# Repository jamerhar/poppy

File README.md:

# Poppy
### 70% Alice keyboard using THT components expanding upon [elmo's Sesame](https://github.com/kb-elmo/sesame).

### Expanding upon the Sesame, the Poppy includes a function row, solenoid support, and a resin printable case.

### Board Bill of Materials
 |Count|Part|Reference|
 |-|-|-|
 |1|ATmega32A 40 Pin DIP|U1|
 |1|40 Pin DIP Socket|U1|
 |1|USB4085-GF-A USB Type-C|J1|
 |1|500mA Polyfuse|F1|
 |2|6mm Push Button|SW1, SW2|
 |1|16MHz Quartz Crystal|X1|
 |1|4.7uF Electrolytic Capacitor|C1|
 |2|0.1uF Ceramic Disk Capacitor|C2,C3|
 |2|22pF Ceramic Disk Capacitor|C4,C5|
 |1|1.5kΩ Resistor|R1|
 |2|68Ω Resistor|R2,R3|
 |2|5.1kΩ Resistor|R4,R5|
 |1|10kΩ Resistor|R6|
 |2|3.6V Zener Diode (DO-35 BZX55C3V6)|D77,D78|
 |76|Universal Switching Diode (DO-35 1N4148)|D1-D76|
 
 This bill of materials is identical to the Sesame's minus the quantity of diodes.
 
 ### Solenoid Bill of Materials
 |Count|Part|Reference|
 |-|-|-|
 |1|Uxcell Mini Push 4.5V @ ~350mA Solenoid| |
 |1|1N4001 Diode|D1|
 |1|TIP120 Transistor|Q1|
 |1|2.2kΩ Resistor|R1|
 
 The solenoid, [purchasable on Amazon](https://www.amazon.com/gp/product/B013DR655A/ref=ppx_yo_dt_b_search_asin_title?ie=UTF8&psc=1), addon is optional and does not employ the most polished mounting and connection to the main PCB, but is functional and supported in both QMK/VIAL firmware. The easiest method is to run wires from the ATmega32A's solenoid pin (B4/pin 5) and +5V and GND from the ISP header above the 32A. Some slight changes to the PCB could be made to add a header or JST connector to the solenoid, but I haven't gotten around to it at this time.
 
 ### Case Bill of Materials
  |Count|Part|
  |-|-|
  |1|PCB|
  |1|Plate|
  |1|Bottom Case (3D/Resin Printed)|
  |1|Top Case (3D/Resin Printed)|
  |1|Weight|
  |4|10mm Diameter Adhesive Bumpons|
  |19|Brass Screw-to-Expand Inserts, M2x4mm|
  |19|M2x5mm Button Head Screw|
  |1|Solenoid Daugherboard PCB (Optional)|
  |1|Solenoid Driver PCB (Optional)|
  |2|M2x3mm Socket/Button Head Screw (Optional)|
  
  8 M2x5mm screws and screw-to-expend inserts, [purchasable on McMaster](https://www.mcmaster.com/94510A611/), are used to secure both halves of the case. 4 M2x5mm screws and inserts are used to secure the plate to the top case. 5 M2x5mm screws and inserts are used to secure the optional solenoid/driver board to the bottom case. 2 M2x3mm screws are used to secure the solenoid to the solenoid daughterboard. 2 M2x5mm screws are used to secure the weight to the bottom case, countersunk holes can be drilled and flat head screws can be used for a flush look. I had my case printed through JLCPCB's resin 3D printing services since I don't have a printer large enough for this board. I've had successful prints with both 8000 resin and 8111X resin, with the latter being cheaper. There is a small amount of warping throughout the thin F-row separating area on both of my prints due to the extremely thin geometry, but it does not interfere during use (YMMV). 
  
### Disclaimer
I do not offer any sort of warranty, nor can I be held liable if something goes wrong.
Please thoroughly review the design, especially involving the case, before ordering anything. There are possibly small errors and other defects within the design, this was my first attempt at case design and it is by no means perfect.

### Additional Images
One revision out of date bottom case:

Weight and solenoid driver wiring:

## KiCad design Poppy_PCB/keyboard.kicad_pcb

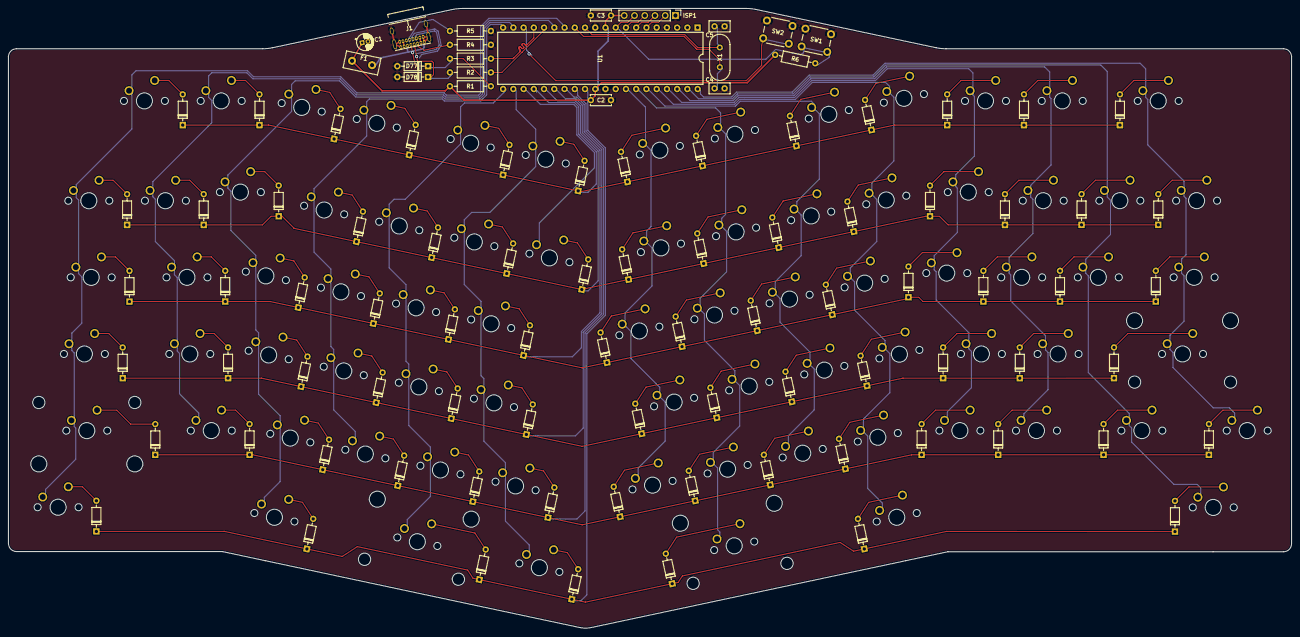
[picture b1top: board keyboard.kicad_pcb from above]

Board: 2 copper layers, 318.4 x 153.8 mm, 172 parts (0 on the bottom side), 113 nets.

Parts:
C1: 4.7u; CP_Radial_D4.0mm_P1.50mm
C2, C3: 0.1u; C_Disc_D5.0mm_W2.5mm_P5.00mm
C4, C5: 22p; C_Disc_D5.0mm_W2.5mm_P2.50mm
D1: F1; D_DO-35_SOD27_P7.62mm_Horizontal
D2: F2; D_DO-35_SOD27_P7.62mm_Horizontal
D3: F3; D_DO-35_SOD27_P7.62mm_Horizontal
D4: F4; D_DO-35_SOD27_P7.62mm_Horizontal
D5: F5; D_DO-35_SOD27_P7.62mm_Horizontal
D6: F6; D_DO-35_SOD27_P7.62mm_Horizontal
D7: F7; D_DO-35_SOD27_P7.62mm_Horizontal
D8: F8; D_DO-35_SOD27_P7.62mm_Horizontal
D9: F9; D_DO-35_SOD27_P7.62mm_Horizontal
D10: F10; D_DO-35_SOD27_P7.62mm_Horizontal
D11: F11; D_DO-35_SOD27_P7.62mm_Horizontal
D12: F12; D_DO-35_SOD27_P7.62mm_Horizontal
D13: F13; D_DO-35_SOD27_P7.62mm_Horizontal
D14: ESC; D_DO-35_SOD27_P7.62mm_Horizontal
D15: 1; D_DO-35_SOD27_P7.62mm_Horizontal
D16: 2; D_DO-35_SOD27_P7.62mm_Horizontal
D17: 3; D_DO-35_SOD27_P7.62mm_Horizontal
D18: 4; D_DO-35_SOD27_P7.62mm_Horizontal
D19: 5; D_DO-35_SOD27_P7.62mm_Horizontal
D20: 6; D_DO-35_SOD27_P7.62mm_Horizontal
D21: 7; D_DO-35_SOD27_P7.62mm_Horizontal
D22: 8; D_DO-35_SOD27_P7.62mm_Horizontal
D23: 9; D_DO-35_SOD27_P7.62mm_Horizontal
D24: 0; D_DO-35_SOD27_P7.62mm_Horizontal
D25: MINS; D_DO-35_SOD27_P7.62mm_Horizontal
D26: EQL; D_DO-35_SOD27_P7.62mm_Horizontal
D27: BSLS; D_DO-35_SOD27_P7.62mm_Horizontal
D28: DEL; D_DO-35_SOD27_P7.62mm_Horizontal
D29: TAB; D_DO-35_SOD27_P7.62mm_Horizontal
D30: Q; D_DO-35_SOD27_P7.62mm_Horizontal
D31: W; D_DO-35_SOD27_P7.62mm_Horizontal
D32: E; D_DO-35_SOD27_P7.62mm_Horizontal
D33: R; D_DO-35_SOD27_P7.62mm_Horizontal
D34: T; D_DO-35_SOD27_P7.62mm_Horizontal
D35: Y; D_DO-35_SOD27_P7.62mm_Horizontal
D36: U; D_DO-35_SOD27_P7.62mm_Horizontal
D37: I; D_DO-35_SOD27_P7.62mm_Horizontal
D38: O; D_DO-35_SOD27_P7.62mm_Horizontal
D39: P; D_DO-35_SOD27_P7.62mm_Horizontal
D40: LBRC; D_DO-35_SOD27_P7.62mm_Horizontal
D41: RBRC; D_DO-35_SOD27_P7.62mm_Horizontal
D42: BSPC; D_DO-35_SOD27_P7.62mm_Horizontal
D43: CAPS; D_DO-35_SOD27_P7.62mm_Horizontal
D44: A; D_DO-35_SOD27_P7.62mm_Horizontal
D45: S; D_DO-35_SOD27_P7.62mm_Horizontal
D46: D; D_DO-35_SOD27_P7.62mm_Horizontal
D47: F; D_DO-35_SOD27_P7.62mm_Horizontal
D48: G; D_DO-35_SOD27_P7.62mm_Horizontal
D49: H; D_DO-35_SOD27_P7.62mm_Horizontal
D50: J; D_DO-35_SOD27_P7.62mm_Horizontal
D51: K; D_DO-35_SOD27_P7.62mm_Horizontal
D52: L; D_DO-35_SOD27_P7.62mm_Horizontal
D53: SCLN; D_DO-35_SOD27_P7.62mm_Horizontal
D54: QUOT; D_DO-35_SOD27_P7.62mm_Horizontal
D55: ENT; D_DO-35_SOD27_P7.62mm_Horizontal
D56: LSFT; D_DO-35_SOD27_P7.62mm_Horizontal
D57: Z; D_DO-35_SOD27_P7.62mm_Horizontal
D58: X; D_DO-35_SOD27_P7.62mm_Horizontal
D59: C; D_DO-35_SOD27_P7.62mm_Horizontal
D60: V; D_DO-35_SOD27_P7.62mm_Horizontal
D61, D62: B; D_DO-35_SOD27_P7.62mm_Horizontal
D63: N; D_DO-35_SOD27_P7.62mm_Horizontal
D64: M; D_DO-35_SOD27_P7.62mm_Horizontal
D65: COMM; D_DO-35_SOD27_P7.62mm_Horizontal
D66: DOT; D_DO-35_SOD27_P7.62mm_Horizontal
D67: SLSH; D_DO-35_SOD27_P7.62mm_Horizontal
D68: RSFT; D_DO-35_SOD27_P7.62mm_Horizontal
D69: FN2; D_DO-35_SOD27_P7.62mm_Horizontal
D70: LCTL; D_DO-35_SOD27_P7.62mm_Horizontal
D71: LALT; D_DO-35_SOD27_P7.62mm_Horizontal
D72: SPC; D_DO-35_SOD27_P7.62mm_Horizontal
D73: LGUI; D_DO-35_SOD27_P7.62mm_Horizontal
D74: FN1; D_DO-35_SOD27_P7.62mm_Horizontal
D75: RALT; D_DO-35_SOD27_P7.62mm_Horizontal
D76: RCTL; D_DO-35_SOD27_P7.62mm_Horizontal
D77, D78: 3.6V; D_DO-35_SOD27_P7.62mm_Horizontal
F1: 500mA; Fuse_Littelfuse_395Series
ISP1: Conn_01x06; PinHeader_1x06_P2.54mm_Vertical
J1: USB_C_Receptacle_USB2.0; USB_C_GCT_USB4085
MX1, MX2, MX3, MX4, MX5, MX6, MX7, MX8, MX9, MX10, MX11, MX12, MX13, MX14, MX15, MX16, MX17, MX18, MX19, MX20, MX21, MX22, MX23, MX24, MX25, MX26, MX27, MX28, MX30, MX31, MX32, MX33, MX34, MX35, MX36, MX37, MX38, MX39, MX40, MX41, MX44, MX45, MX46, MX47, MX48, MX49, MX50, MX51, MX52, MX53, MX54, MX57, MX58, MX59, MX60, MX61, MX62, MX63, MX64, MX65, MX66, MX67, MX69, MX73: KEYSW; MXOnly-1U-NoLED
MX29, MX42, MX70, MX71, MX75, MX76: KEYSW; MXOnly-1.5U-NoLED
MX43, MX68: KEYSW; MXOnly-1.75U-NoLED
MX55, MX72: KEYSW; MXOnly-2.25U-ReversedStabilizers-NoLED
MX56: KEYSW; MXOnly-2.25U-NoLED
MX74: KEYSW; MXOnly-2.75U-ReversedStabilizers-NoLED
R1: 1.5K; R_Axial_DIN0207_L6.3mm_D2.5mm_P10.16mm_Horizontal
R2, R3: 68; R_Axial_DIN0207_L6.3mm_D2.5mm_P10.16mm_Horizontal
R4, R5: 5.1K; R_Axial_DIN0207_L6.3mm_D2.5mm_P10.16mm_Horizontal
R6: 10K; R_Axial_DIN0207_L6.3mm_D2.5mm_P10.16mm_Horizontal
SW1: RESET; SW_PUSH_6mm
SW2: BOOT; SW_PUSH_6mm
U1: ATmega32A-PU; DIP-40_W15.24mm
X1: Crystal; Crystal_HC49-4H_Vertical

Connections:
+5V: C1.1, C2.1, C3.1, F1.1, ISP1.6, R1.2, R6.1, U1.10, U1.30
BOOT: SW2.2, U1.18
D+: R2.1, U1.16
D-: R3.1, U1.17
GND: C1.2, C2.2, C3.2, C4.2, C5.2, D77.2, D78.2, ISP1.1, J1.A1, J1.A12, J1.B1, J1.B12, J1.S1, R4.1, R5.1, SW1.1, SW2.1, U1.11, U1.31
MISO: ISP1.3, U1.7
MOSI: ISP1.2, U1.6
unnamed: C4.1, U1.13, X1.2
unnamed: C5.1, U1.12, X1.1
unnamed: D1.2, MX1.2
unnamed: D2.2, MX2.2
unnamed: D3.2, MX3.2
unnamed: D4.2, MX4.2
unnamed: D5.2, MX5.2
unnamed: D6.2, MX6.2
unnamed: D7.2, MX7.2
unnamed: D8.2, MX8.2
unnamed: D9.2, MX9.2
unnamed: D10.2, MX10.2
unnamed: D11.2, MX11.2
unnamed: D12.2, MX12.2
unnamed: D13.2, MX13.2
unnamed: D14.2, MX14.2
unnamed: D15.2, MX15.2
unnamed: D16.2, MX16.2
unnamed: D17.2, MX17.2
unnamed: D18.2, MX18.2
unnamed: D19.2, MX19.2
unnamed: D20.2, MX20.2
unnamed: D21.2, MX21.2
unnamed: D22.2, MX22.2
unnamed: D23.2, MX23.2
unnamed: D24.2, MX24.2
unnamed: D25.2, MX25.2
unnamed: D26.2, MX26.2
unnamed: D27.2, MX27.2
unnamed: D28.2, MX28.2
unnamed: D29.2, MX29.2
unnamed: D30.2, MX30.2
unnamed: D31.2, MX31.2
unnamed: D32.2, MX32.2
unnamed: D33.2, MX33.2
unnamed: D34.2, MX34.2
unnamed: D35.2, MX35.2
unnamed: D36.2, MX36.2
unnamed: D37.2, MX37.2
unnamed: D38.2, MX38.2
unnamed: D39.2, MX39.2
unnamed: D40.2, MX40.2
unnamed: D41.2, MX41.2
unnamed: D42.2, MX42.2
unnamed: D43.2, MX43.2
unnamed: D44.2, MX44.2
unnamed: D45.2, MX45.2
unnamed: D46.2, MX46.2
unnamed: D47.2, MX47.2
unnamed: D48.2, MX48.2
unnamed: D49.2, MX49.2
unnamed: D50.2, MX50.2
unnamed: D51.2, MX51.2
unnamed: D52.2, MX52.2
unnamed: D53.2, MX53.2
unnamed: D54.2, MX54.2
unnamed: D55.2, MX55.2
unnamed: D56.2, MX56.2
unnamed: D57.2, MX57.2
unnamed: D58.2, MX58.2
unnamed: D59.2, MX59.2
unnamed: D60.2, MX60.2
unnamed: D61.2, MX61.2
unnamed: D62.2, MX62.2
unnamed: D63.2, MX63.2
unnamed: D64.2, MX64.2
unnamed: D65.2, MX65.2
unnamed: D66.2, MX66.2
unnamed: D67.2, MX67.2
unnamed: D68.2, MX68.2
unnamed: D69.2, MX69.2
unnamed: D70.2, MX70.2
unnamed: D71.2, MX71.2
unnamed: D72.2, MX72.2
unnamed: D73.2, MX73.2
unnamed: D74.2, MX74.2
unnamed: D75.2, MX75.2
unnamed: D76.2, MX76.2
unnamed: D77.1, J1.A7, J1.B7, R1.1, R3.2
unnamed: D78.1, J1.A6, J1.B6, R2.2
unnamed: J1.A5, R4.2
unnamed: J1.B5, R5.2
RESET: ISP1.5, R6.2, SW1.2, U1.9
SCK: ISP1.4, U1.8
VCC: F1.2, J1.A4, J1.A9, J1.B4, J1.B9
col0: MX1.1, MX14.1, MX29.1, MX43.1, MX56.1, MX70.1, U1.14
col1: MX2.1, MX15.1, MX30.1, MX44.1, MX57.1, U1.15
col2: MX3.1, MX16.1, MX31.1, MX45.1, MX58.1, MX71.1, U1.19
col3: MX4.1, MX17.1, MX32.1, MX46.1, MX59.1, U1.20
col4: MX5.1, MX18.1, MX33.1, MX47.1, MX60.1, MX72.1, U1.21
col5: MX6.1, MX19.1, MX34.1, MX48.1, MX61.1, MX73.1, U1.22
col6: MX20.1, U1.23
col7: MX7.1, MX21.1, MX35.1, MX49.1, MX62.1, U1.33
col8: MX8.1, MX22.1, MX36.1, MX50.1, MX63.1, MX74.1, U1.34
col9: MX9.1, MX23.1, MX37.1, MX51.1, MX64.1, U1.35
col10: MX10.1, MX24.1, MX38.1, MX52.1, MX65.1, MX75.1, U1.36
col11: MX11.1, MX25.1, MX39.1, MX53.1, MX66.1, U1.37
col12: MX12.1, MX26.1, MX40.1, MX54.1, MX67.1, U1.38
col13: MX27.1, MX41.1, MX68.1, MX76.1, U1.39
col14: MX13.1, MX28.1, MX42.1, MX55.1, MX69.1, U1.40
row0: D1.1, D2.1, D3.1, D4.1, D5.1, D6.1, D7.1, D8.1, D9.1, D10.1, D11.1, D12.1, D13.1, U1.24
row1: D14.1, D15.1, D16.1, D17.1, D18.1, D19.1, D20.1, D21.1, D22.1, D23.1, D24.1, D25.1, D26.1, D27.1, D28.1, U1.25
row2: D29.1, D30.1, D31.1, D32.1, D33.1, D34.1, D35.1, D36.1, D37.1, D38.1, D39.1, D40.1, D41.1, D42.1, U1.26
row3: D43.1, D44.1, D45.1, D46.1, D47.1, D48.1, D49.1, D50.1, D51.1, D52.1, D53.1, D54.1, D55.1, U1.27
row4: D56.1, D57.1, D58.1, D59.1, D60.1, D61.1, D62.1, D63.1, D64.1, D65.1, D66.1, D67.1, D68.1, D69.1, U1.28
row5: D70.1, D71.1, D72.1, D73.1, D74.1, D75.1, D76.1, U1.29
